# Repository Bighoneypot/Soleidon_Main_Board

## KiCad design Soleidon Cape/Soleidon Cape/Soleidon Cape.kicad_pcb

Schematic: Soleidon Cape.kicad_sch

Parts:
C1, C2, C3, C4, C5, C6, C7, C8: 100nF; C_0201_0603Metric
C9, C10, C11, C12, C13, C14, C15, C16, C17, C18, C19, C20, C21, C22, C23, C24, C25, C26, C27, C28, C29, C30, C31, C32: 22nF; C_0201_0603Metric
C33, C34, C35, C36, C37, C38, C39, C40: C100 nF; C_0201_0603Metric
C41, C55, C56: 10μF; C_0805_2012Metric
C42: C220uF/35V; PCAP_8x10-ELECT_NCA; Part number UWT1V221MNL1GS
C43: 100pF; C_0201_0603Metric
C44: 2.2nF; C_0201_0603Metric
C45: 10uF; C_0201_0603Metric
C46: 10nF; C_0201_0603Metric
C47: 100nf; C_0201_0603Metric
C48: 0.1μF; C_0805_2012Metric
C49: 220uF 50V; CAP_6.3 X 5.8_PAN
C50: 1uF; C_0201_0603Metric
C51: 470nF; C_0201_0603Metric
C52, C58: 22 µF X7R; C_0201_0603Metric
C53: 470pF; C_0805_2012Metric
C54: C220uF/35V; PCAP_8x10-ELECT_NCA; Part number 5YXF220MEFC Rubycon
C57: 220 µF/10 V; PCAP_8x10-ELECT_NCA
D1, D2, D3, D4, D5, D6, D7, D8: D_Zener_4.7V; D_SOD-123
D9, D10: LTST-C190KRKT; LED_0603_1608Metric
D11: MBRS340; D_SMC
D12: Z2SMBxxx; D_SMB
D13: P6SMB33A; DIOM4336X265N; PARTREV F2102
D14: D_Schottky; SMA_DIO_schottky; Part number B240A-13-F
D15: SS54; D_SMA
D16: LED; LED_0603_1608Metric
F1: 01550900DR; FUSE_155900_LTF
H1, H2, H3, H4, H5, H6: MountingHole; MountingHole_3.2mm_M3
J1, J2, J8, J9, J13, J14, J15, J16: Conn_01x01_Socket; PinHeader_1x01_P2.54mm_Vertical
J3: U1_4-20mA; CUI_TBL009-254-04GY-2GY; DigiKey_Part_Number 102-TBL009-254-04GY-2GY-ND
J4: U8_4-20mA; CUI_TBL009-254-04GY-2GY; DigiKey_Part_Number 102-TBL009-254-04GY-2GY-ND
J5: U2_0-5V; CUI_TBL009-254-04GY-2GY; DigiKey_Part_Number 102-TBL009-254-04GY-2GY-ND
J6: U5_0-5V; CUI_TBL009-254-04GY-2GY; DigiKey_Part_Number 102-TBL009-254-04GY-2GY-ND
J7: U6_0-5V; CUI_TBL009-254-04GY-2GY; DigiKey_Part_Number 102-TBL009-254-04GY-2GY-ND
J10: U7_0-5V; CUI_TBL009-254-04GY-2GY; DigiKey_Part_Number 102-TBL009-254-04GY-2GY-ND
J11: U3_0-5V; CUI_TBL009-254-04GY-2GY; DigiKey_Part_Number 102-TBL009-254-04GY-2GY-ND
J12: U4_0-5V; CUI_TBL009-254-04GY-2GY; DigiKey_Part_Number 102-TBL009-254-04GY-2GY-ND
J17: PowerOnOff for Sensors; PinHeader_1x02_P2.54mm_Vertical
J18: 2601-1102; CONN2_2601-1102_WAG
J19, J20, J21, J23, J24, J25, J26, J27, J28: PRT-14417; QWIIC-SPARKFUN_PRT-14417; PARTREV NA
J22: Power OnOff StepDown; PinHeader_1x02_P2.54mm_Vertical
J29, J30: 2-644803-3; TE_2-644803-3; PARTREV R
J31, J32, J33, J35, J36, J37, J39, J40: Power 24V; CONN_1841513
J34: Power 3.3V; CONN_1841513
J38: Power 5V; CONN_1841513
JP1, JP2, JP3, JP4, JP5, JP6, JP7, JP8, JP9, JP10, JP11, JP12, JP13, JP14, JP15, JP16, JP20, JP21, JP22, JP23, JP24, JP25, JP26, JP27, JP28, JP29, JP30, JP35, JP36, JP37, JP38, JP39, JP40, JP41, JP42: SolderJumper_2_Open; SolderJumper-2_P1.3mm_Open_TrianglePad1.0x1.5mm
JP17, JP18, JP19, JP31, JP32, JP33, JP34: SolderJumper_2_Open; Custom_Open_Jumper
JP43: SolderJumper_2_Open; SolderJumper-2_P1.3mm_Open_RoundedPad1.0x1.5mm
L1: 82 μH; RL622_Series; Part number RL622-820K-RC Bourns
L1_SRR1260-330M1: 33 µH; IND_BOURNS_SRR1260
LED1: LED; LED_0603_1608Metric
Q1, Q2, Q3, Q4: BSS138; SOT-23
R1, R2, R3, R4, R5, R6, R7, R8: R10k; R_0603_1608Metric
R9, R10, R43, R44, R45, R46, R47, R48: R0; R_0603_1608Metric
R11, R12, R13, R14, R15, R16, R17, R18, R19, R20, R21, R22, R23, R24, R25, R26, R27, R28, R29, R30, R31, R32, R33, R34: R470Ω; R_0603_1608Metric
R35, R36, R37, R38, R39, R40, R41, R42: 180Ω; R_0603_1608Metric
R49, R50, R51, R52, R53, R59, R61, R68: 10K; R_0603_1608Metric
R54: R100K; C_0201_0603Metric
R55: 4.7kΩ; R_0201_0603Metric
R56: 8.2kΩ; R_1206_3216Metric
R57: R47k; C_0201_0603Metric
R58, R60: 4.7kΩ; R_0603_1608Metric
R62, R64, R65: R0; C_0201_0603Metric
R63: R100Ω; R_0603_1608Metric
R66: R3.8K; C_0201_0603Metric
R67: 100 kΩ; R_0603_1608Metric
R69: 680 Ω; R_0201_0603Metric
R70: 220Ω; R_0201_0603Metric
R71, R72, R73, R74, R75, R76, R77, R78: 4.7kΩ; R_0805_2012Metric
TP1, TP2, TP4, TP7, TP8, TP9, TP11, TP12, TP13, TP14, TP16: TestPoint; TestPoint_Pad_1.5x1.5mm
TP3: 24Vin; TestPoint_Pad_1.5x1.5mm
TP5, TP6: 24Vout; TestPoint_Pad_1.5x1.5mm
TP10: TestPoint_2Pole; PinHeader_1x02_P2.54mm_Vertical
TP15: TestPoint -GND_5V; TestPoint_Pad_1.5x1.5mm
TP17: TestPoint +5V; TestPoint_Pad_1.5x1.5mm
U1, U2, U3, U4, U5, U6, U7, U8: ADS1115IDGSR; DGS0010A_N
U9: TPS5403; SOIC-8_3.9x4.9mm_P1.27mm
U10: PCA9546A TSSOP; D16_TEX
VR1: LM2596S-5.0_NOPB; PARTREV E

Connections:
+3.3V: C45.1, C47.1, C54.1, C55.1, C56.1, J23.2, J24.2, J34.5, J34.6, J34.7, J34.8, JP11.2 (B), JP12.1 (A), JP13.2 (B), JP17.1 (A), JP18.1 (A), JP19.1 (A), JP24.2 (B), JP26.1 (A), JP31.1 (A), JP32.1 (A), JP33.1 (A), JP34.1 (A), L1.2, Q1.1 (G), Q2.1 (G), Q3.1 (G), Q4.1 (G), R58.2, R60.2, R64.1, R68.2, R70.2, R71.1, R72.1, R75.1, R76.1, TP8.1, TP11.1, U10.16 (VCC)
+24V: F1.1, J18.1 (1_1), J18.2 (1_2), TP3.1, TP5.1
+24V_PowerSensor_OUT: J17.1, J31.5, J31.6, J31.7, J31.8, J32.5, J32.6, J32.7, J32.8, J33.5, J33.6, J33.7, J33.8, J35.5, J35.6, J35.7, J35.8, J36.5, J36.6, J36.7, J36.8, J37.5, J37.6, J37.7, J37.8, J39.5, J39.6, J39.7, J39.8, J40.5, J40.6, J40.7, J40.8, R55.1
+24_PROTECT: C41.1, C42.1, C49.1, C50.1, C51.2, D12.1 (K), D13.C, J17.2, J22.2, R56.2, TP2.1, TP6.1, U9.2 (VIN), VR1.1 (VIN)
/2SCL: J23.4, U10.10 (SC2)
/2SDA: J23.3, U10.9 (SD2)
/3SCL: J24.4, U10.12 (SC3)
/3SDA: J24.3, U10.11 (SD3)
/A0: JP12.2 (B), R52.2, U10.1 (A0)
/A1: JP13.1 (A), R51.2, U10.2 (A1)
/A2: JP11.1 (A), R50.2, U10.13 (A2)
ADDR_U8: R46.1, U5.1 (ADDR)
ADDR_U9: R48.1, U6.1 (ADDR)
ADDR_U10: R44.1, U2.1 (ADDR)
ADDR_U11: R45.1, U3.1 (ADDR)
ADDR_U13: R47.1, U4.1 (ADDR)
ADDR_U14: R43.1, U7.1 (ADDR)
ADDR_U16: R10.1, U8.1 (ADDR)
ADDR_U17: R9.1, U1.1 (ADDR)
AIN0_U8: J6.1_A (1), J6.1_B (1), R11.2
AIN0_U9: J7.1_A (1), J7.1_B (1), R16.2
AIN0_U10: J5.1_A (1), J5.1_B (1), R13.2
AIN0_U11: J11.1_A (1), J11.1_B (1), R19.2
AIN0_U13: J12.1_A (1), J12.1_B (1), R23.2
AIN0_U14: J10.1_A (1), J10.1_B (1), R27.2
AIN0_U16: C40.2, D8.2 (A), J4.1_A (1), J4.1_B (1), R42.2, U8.4 (AIN0)
AIN0_U17: C36.2, D4.2 (A), J3.1_A (1), J3.1_B (1), R38.2, U1.4 (AIN0)
AIN1_U8: J6.2_A (2), J6.2_B (2), R31.2
AIN1_U9: J7.2_A (2), J7.2_B (2), R17.2
AIN1_U10: J5.2_A (2), J5.2_B (2), R34.2
AIN1_U11: J11.2_A (2), J11.2_B (2), R20.2
AIN1_U13: J12.2_A (2), J12.2_B (2), R24.2
AIN1_U14: J10.2_A (2), J10.2_B (2), R28.2
AIN1_U16: C39.2, D7.2 (A), J4.2_A (2), J4.2_B (2), R41.2, U8.5 (AIN1)
AIN1_U17: C35.2, D3.2 (A), J3.2_A (2), J3.2_B (2), R37.2, U1.5 (AIN1)
AIN2_U8: J6.3_A (3), J6.3_B (3), R32.2
AIN2_U9: J7.3_A (3), J7.3_B (3), R33.2
AIN2_U10: J5.3_A (3), J5.3_B (3), R14.2
AIN2_U11: J11.3_A (3), J11.3_B (3), R21.2
AIN2_U13: J12.3_A (3), J12.3_B (3), R25.2
AIN2_U14: J10.3_A (3), J10.3_B (3), R29.2
AIN2_U16: C38.2, D6.2 (A), J4.3_A (3), J4.3_B (3), R40.2, U8.6 (AIN2)
AIN2_U17: C34.2, D2.2 (A), J3.3_A (3), J3.3_B (3), R36.2, U1.6 (AIN2)
AIN3_U8: J6.4_A (4), J6.4_B (4), R12.2
AIN3_U9: J7.4_A (4), J7.4_B (4), R18.2
AIN3_U10: J5.4_A (4), J5.4_B (4), R15.2
AIN3_U11: J11.4_A (4), J11.4_B (4), R22.2
AIN3_U13: J12.4_A (4), J12.4_B (4), R26.2
AIN3_U14: J10.4_A (4), J10.4_B (4), R30.2
AIN3_U16: C37.2, D5.2 (A), J4.4_A (4), J4.4_B (4), R39.2, U8.7 (AIN3)
AIN3_U17: C33.2, D1.2 (A), J3.4_A (4), J3.4_B (4), R35.2, U1.7 (AIN3)
ALERT/RDY_U8: J14.1, R5.2, U5.2 (ALERT_RDY)
ALERT/RDY_U10: J9.1, R1.2, U2.2 (ALERT_RDY)
ALERT/RDY_U11: J15.1, R2.2, U3.2 (ALERT_RDY)
ALERT/RDY_U13: J16.1, R3.2, U4.2 (ALERT_RDY)
ALERT/RDY_U14: J13.1, R7.2, U7.2 (ALERT_RDY)
ALERT/RDY_U16: J2.1, R8.2, U8.2 (ALERT_RDY)
ALERT/RDY_U17: J1.1, R4.2, U1.2 (ALERT_RDY)
EXT_5V: C1.1, C2.1, C3.1, C4.1, C5.2, C6.1, C7.1, C8.1, C57.1, C58.1, D15.1 (K), J38.5, J38.6, J38.7, J38.8, JP1.1 (A), JP2.1 (A), JP3.1 (A), JP4.1 (A), JP5.1 (A), JP6.1 (A), JP7.1 (A), JP8.1 (A), JP9.2 (B), JP10.1 (A), JP39.1 (A), JP40.2 (B), JP41.1 (A), JP42.2 (B), L1_SRR1260-330M1.1, L1_SRR1260-330M1.2, R43.2, R48.2, R69.2, R73.1, R74.1, R77.1, R78.2, TP9.1, TP10.2, TP17.1, U1.8 (VDD), U2.8 (VDD), U3.8 (VDD), U4.8 (VDD), U5.8 (VDD), U6.8 (VDD), U7.8 (VDD), U8.8 (VDD), VR1.2 (OUTPUT), VR1.4 (FEEDBACK)
GND: C1.2, C2.2, C3.2, C4.2, C5.1, C6.2, C7.2, C8.2, C9.2, C10.2, C11.2, C12.2, C13.2, C14.2, C15.2, C16.2, C17.2, C18.2, C19.2, C20.2, C21.2, C22.2, C23.2, C24.2, C25.2, C26.2, C27.2, C28.2, C29.2, C30.2, C31.2, C32.2, C33.1, C34.1, C35.1, C36.1, C37.1, C38.1, C39.1, C40.1, C41.2, C42.2, C43.2, C44.2, C45.2, C46.2, C47.2, C49.2, C50.2, C51.1, C54.2, C55.2, C56.2, C57.2, C58.2, D1.1 (K), D2.1 (K), D3.1 (K), D4.1 (K), D5.1 (K), D6.1 (K), D7.1 (K), D8.1 (K), D9.1 (C), D10.1 (C), D12.2 (A), D13.A, D14.2 (A), D15.2 (A), D16.1 (K), J18.3 (2_1), J18.4 (2_2), J19.1, J20.1, J21.1, J23.1, J24.1, J25.1, J26.1, J27.1, J28.1, J29.2, J30.2, J31.1, J31.2, J31.3, J31.4, J32.1, J32.2, J32.3, J32.4, J33.1, J33.2, J33.3, J33.4, J34.1, J34.2, J34.3, J34.4, J35.1, J35.2, J35.3, J35.4, J36.1, J36.2, J36.3, J36.4, J37.1, J37.2, J37.3, J37.4, J38.1, J38.2, J38.3, J38.4, J39.1, J39.2, J39.3, J39.4, J40.1, J40.2, J40.3, J40.4, LED1.1 (K), R35.1, R36.1, R37.1, R38.1, R39.1, R40.1, R41.1, R42.1, R46.2, R47.2, R50.1, R51.1, R52.1, R54.2, R66.2, R67.1, TP1.1, TP4.1, TP10.1, TP12.1, TP15.1, TP16.1, U1.3 (GND), U2.3 (GND), U3.3 (GND), U4.3 (GND), U5.3 (GND), U6.3 (GND), U7.3 (GND), U8.3 (GND), U9.7 (GND), U10.8 (GND), VR1.3 (GROUND), VR1.5 (~ON/OFF), VR1.6 (GND_TAB)
unnamed: C44.1, R57.2
unnamed: C48.2, R62.2
unnamed: C53.1, R64.2, R65.1, TP7.1
unnamed: D9.2 (A), R56.1
unnamed: D10.2 (A), R55.2
unnamed: D11.2 (A), F1.2
unnamed: D11.1 (K), J22.1
unnamed: C48.1, D14.1 (K), L1.1, U9.8 (LX)
unnamed: D16.2 (A), R69.1
unnamed: J29.1, J30.1, TP13.1
unnamed: J29.3, J30.3, TP14.1
unnamed: JP1.2 (B), R1.1
unnamed: JP2.2 (B), R3.1
unnamed: JP3.2 (B), R6.1
unnamed: JP4.2 (B), R2.1
unnamed: JP5.2 (B), R7.1
unnamed: JP6.2 (B), R4.1
unnamed: JP7.2 (B), R5.1
unnamed: JP8.2 (B), R8.1
unnamed: JP9.1 (A), R49.2
unnamed: JP10.2 (B), R53.1
unnamed: J19.3, JP14.2 (B)
unnamed: J20.3, JP15.2 (B)
unnamed: J21.3, JP16.2 (B)
unnamed: J21.2, JP17.2 (B)
unnamed: J19.2, JP18.2 (B)
unnamed: J20.2, JP19.2 (B)
unnamed: J19.4, JP20.2 (B)
unnamed: J20.4, JP21.2 (B)
unnamed: J21.4, JP22.2 (B)
unnamed: JP23.2 (B), R58.1
unnamed: JP24.1 (A), R59.2
unnamed: JP25.2 (B), R60.1
unnamed: JP26.2 (B), R61.1
unnamed: J26.3, JP27.2 (B)
unnamed: J27.3, JP28.2 (B)
unnamed: J25.4, JP29.2 (B)
unnamed: J28.3, JP30.2 (B)
unnamed: J25.2, JP31.2 (B)
unnamed: J26.2, JP32.2 (B)
unnamed: J27.2, JP33.2 (B)
unnamed: J28.2, JP34.2 (B)
unnamed: J26.4, JP35.2 (B)
unnamed: J27.4, JP36.2 (B)
unnamed: J25.3, JP37.2 (B)
unnamed: J28.4, JP38.2 (B)
unnamed: JP39.2 (B), R63.2
unnamed: C52.1, JP40.1 (A)
unnamed: JP41.2 (B), R63.1
unnamed: C52.2, JP42.1 (A)
unnamed: JP43.1 (A), R67.2
unnamed: JP43.2 (B), R68.1, U10.3 (*RESET)
unnamed: LED1.2 (A), R70.1
unnamed: C14.1, R13.1, U2.4 (AIN0)
unnamed: C32.1, R34.1, U2.5 (AIN1)
unnamed: C15.1, R14.1, U2.6 (AIN2)
unnamed: C11.1, R15.1, U2.7 (AIN3)
unnamed: C23.1, R19.1, U3.4 (AIN0)
unnamed: C24.1, R20.1, U3.5 (AIN1)
unnamed: C25.1, R21.1, U3.6 (AIN2)
unnamed: C26.1, R22.1, U3.7 (AIN3)
unnamed: C27.1, R23.1, U4.4 (AIN0)
unnamed: C16.1, R24.1, U4.5 (AIN1)
unnamed: C28.1, R25.1, U4.6 (AIN2)
unnamed: C29.1, R26.1, U4.7 (AIN3)
unnamed: C9.1, R11.1, U5.4 (AIN0)
unnamed: C20.1, R31.1, U5.5 (AIN1)
unnamed: C30.1, R32.1, U5.6 (AIN2)
unnamed: C10.1, R12.1, U5.7 (AIN3)
unnamed: C13.1, R16.1, U6.4 (AIN0)
unnamed: C21.1, R17.1, U6.5 (AIN1)
unnamed: C22.1, C31.1, R18.1, R33.1, U6.6 (AIN2), U6.7 (AIN3)
unnamed: C17.1, R27.1, U7.4 (AIN0)
unnamed: C18.1, R28.1, U7.5 (AIN1)
unnamed: C12.1, R29.1, U7.6 (AIN2)
unnamed: C19.1, R30.1, U7.7 (AIN3)
unnamed: R62.1, U9.1 (BOOT)
unnamed: C43.1, R57.1, U9.6 (COMP)
unnamed: R54.1, U9.3 (ROSC)
unnamed: C46.1, U9.4 (SS)
unnamed: C53.2, R65.2, R66.1, U9.5 (VSENSE)
SCL: R49.1, R59.1
SCL_0: Q3.2 (S), R75.2, U10.4 (SD0)
SCL_1: Q4.2 (S), R76.2, U10.7 (SC1)
SCL_ADS_1: Q4.3 (D), R9.2, R78.1, U1.9 (SDA), U1.10 (SCL), U2.9 (SDA), U2.10 (SCL), U3.9 (SDA), U3.10 (SCL), U4.9 (SDA), U4.10 (SCL), U5.9 (SDA), U5.10 (SCL), U6.9 (SDA), U6.10 (SCL), U7.9 (SDA), U7.10 (SCL), U8.9 (SDA), U8.10 (SCL)
SCL_EXT: JP23.1 (A), JP29.1 (A), U10.14 (SCL)
SCL_EXT2: JP20.1 (A), JP35.1 (A)
SCL_EXT3: JP21.1 (A), JP36.1 (A)
SCL_EXT4: JP22.1 (A), JP38.1 (A)
SCL__ADS_0: Q3.3 (D), R45.2, R77.2
SDA: R53.2, R61.2
SDA_0: Q1.2 (S), R71.2, U10.5 (SC0)
SDA_1: Q2.2 (S), R72.2, U10.6 (SD1)
SDA_ADS_0: Q1.3 (D), R44.2, R73.2
SDA_ADS_1: Q2.3 (D), R10.2, R74.2
SDA_EXT: JP25.1 (A), JP37.1 (A), U10.15 (SDA)
SDA_EXT_2: JP14.1 (A), JP15.1 (A), JP16.1 (A), JP27.1 (A), JP28.1 (A), JP30.1 (A)

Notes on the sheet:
I2C ADDRESS JUMPER
Important!!! zener (<100 pF)
Level Shifter SDA1
*****FIRST ADS1115****
HEADER
Dettaglio layout (importante ora) C19 e C20 → attaccati ai pin 1 (VIN) e 3 (GND) del regolatore. L1 e D12 → compattissimi tra i pin 2 (OUT) e 4 (SW). C21 e C22 → subito dopo L1, con collegamento diretto al piano GND. D10 (TVS) → fisicamente vicino al connettore d'ingresso, prima del fusibile. Piano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
0x4B
ADS TO READ 4-20mA
Sensor 4-20mA
ADC ADS1115
0x4A
MOUNTING HOLES
I²C_MUX
Separazione funzionale “fisica” Nel layer 2, puoi sagomare il piano GND per creare piccole “colle” o “colli” di rame che delimitano le zone: 🔵 Zona Analogica (ADS1115, 4–20 mA) → ritorni filtrati e puliti. 🟠 Zona Digitale (PCA9546A, I²C, LED, MCU) → correnti impulsive. ➡️ Queste due zone non devono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
Ampia area di rame GND attorno al condensatore bulk (es. C49 220 µF). Da questa zona partono: il GND dello step-down 24→5 V, il GND del TPS5403 (5→3.3 V), e il piano GND generale del layer 2.
Level Shifter SDA0
0x48
I2C PULL-UP 5V YES/NO
0x49
I2C PULL-UP 3V YES/NO

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
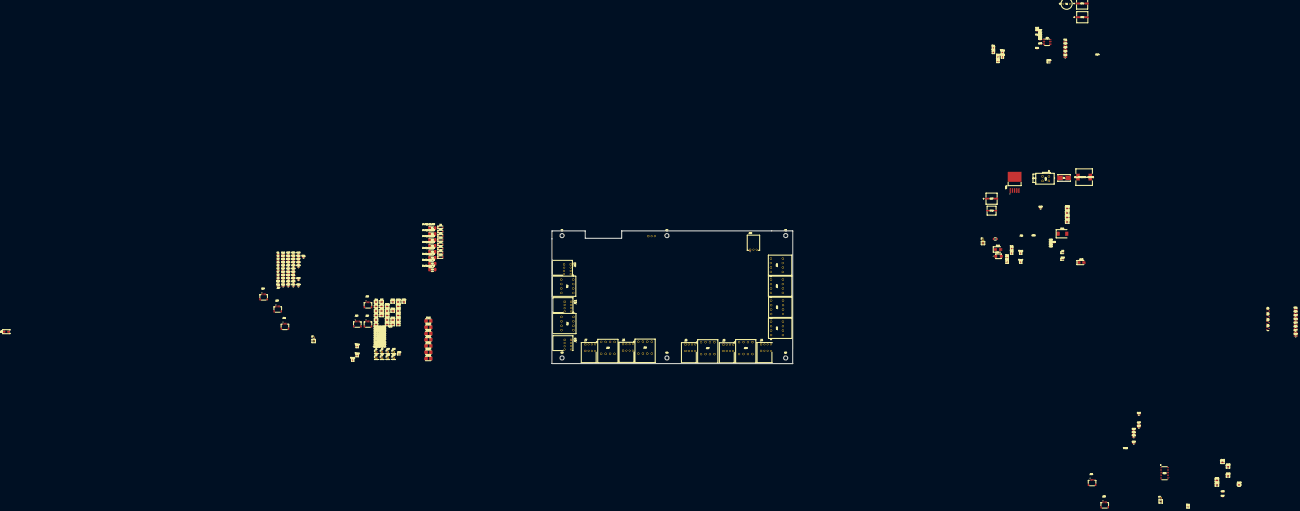
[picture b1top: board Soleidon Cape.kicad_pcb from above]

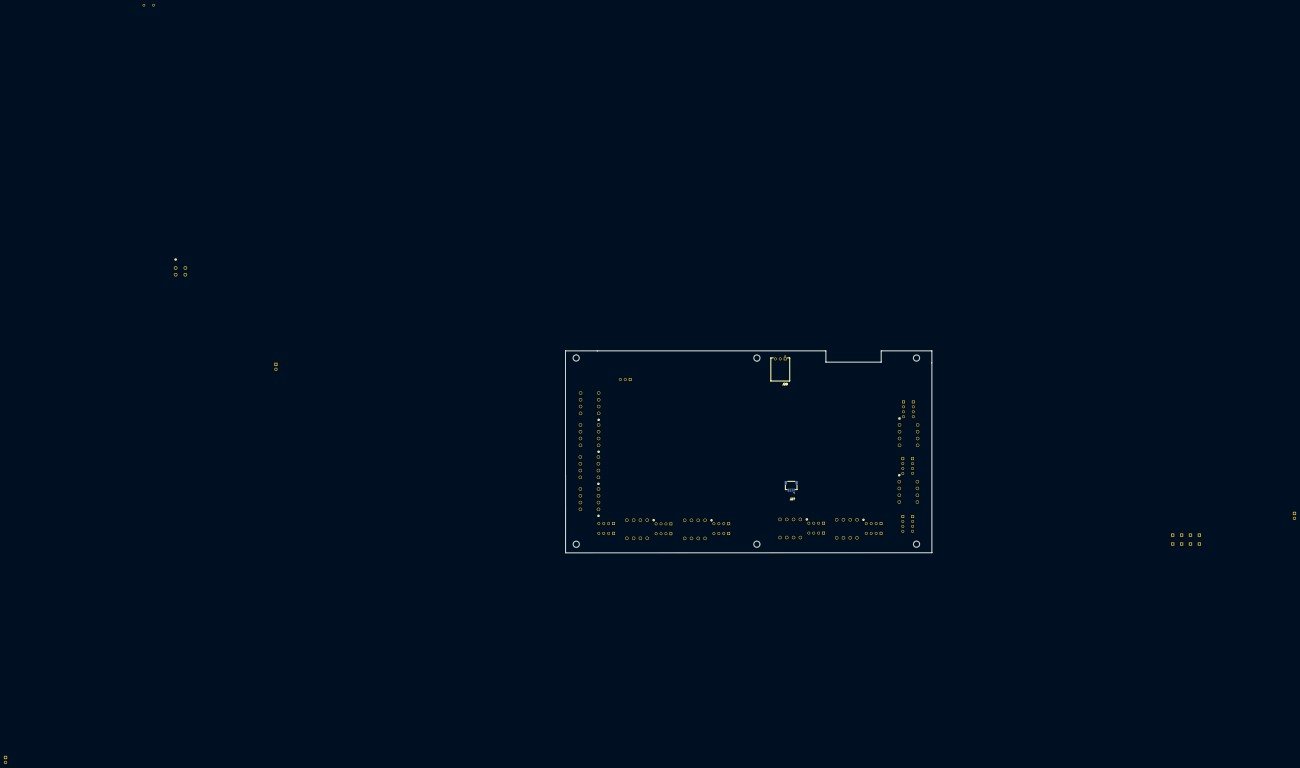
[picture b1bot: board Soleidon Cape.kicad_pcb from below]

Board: 4 copper layers, 277 parts (2 on the bottom side), 158 nets, no tracks yet.

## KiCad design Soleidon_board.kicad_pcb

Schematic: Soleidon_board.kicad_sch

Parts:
C1, C2, C3, C4, C5, C6, C8, C10, C11, C12, C13: 104; C_0805_2012Metric_Pad1.18x1.45mm_HandSolder
C7: 1uF ±10% 50V; CL21A226MAQNNNE; Manufacturer Part CL10A105KB8NNNC; LCSC Part Name 1uF ±10% 50V
C9: 22uF ±20% 25V; CL21A226MAQNNNE; Manufacturer Part CL21A226MAQNNNE; LCSC Part Name 22uF ±20% 25V
C14: 10uF ±10% 16V; CL21A226MAQNNNE; Manufacturer Part CL21A106KOQNNNE; LCSC Part Name 10uF ±10% 16V
CARD1: micro SD-CARD TF PUSH; TF-SMD_TF-PUSH; Manufacturer Part TF PUSH; LCSC Part Name 自弹式 MicroSD卡(TF卡) 卡座
D1, D2, D3: RB168MM-40TR; RB168MM-40TR___SOD-123FL_L2.6-W1.6-LS3.5-RD; Manufacturer Part RB168MM-40TR; LCSC Part Name 电压:40V 电流:1A
H1, H2, H3, H4: MountingHole; MountingHole_3.2mm_M3_ISO14580_Pad_TopOnly
H5: Header-Female-2.54_1x2; PinHeader_1x02_P2.54mm_Vertical; Manufacturer Part 2.54-1*3P母; LCSC Part Name 间距:2.54mm 直插; not fitted
H6: Header-Female-2.54_1x6; PinHeader_1x03_P2.54mm_Vertical; Manufacturer Part 2.54-1*6P母; LCSC Part Name 间距:2.54mm 1x6P 直插; not fitted
H7: Header-Female-2.54_1x3; PinHeader_1x03_P2.54mm_Vertical; Manufacturer Part 2.54-1*3P母; LCSC Part Name 间距:2.54mm 直插; not fitted
H8: Header-Female-2.54_1x2; PinHeader_1x02_P2.54mm_Vertical; Manufacturer Part 2.54-1*2P母; LCSC Part Name 间距:2.54mm 1x2P 直插; not fitted
J1, J2, J3, J4: SM04B-SRSS-TB; CONN_SM04B-SRSS-TB_JST
LED1: TJ-S1615CY6TGLCCSRGB-A5; LED-ARRAY-SMD_4P-L1.6-W1.5-BL-FD; Manufacturer Part TJ-S1615CY6TGLCCSRGB-A5; LCSC Part Name RGB三色
PowerConn1: Header-Female-2.54_1x2; PinSocket_1x03_P2.54mm_Vertical; Manufacturer Part 2.54-1*2P母; LCSC Part Name 间距:2.54mm 1x2P 直插
Q1: PMOSFET-DMP1045U-7; DMP1045_SOT-23-3_L2.9-W1.3-P1.90-LS2.4-BR; Manufacturer Part DMP1045U-7; LCSC Part Name 1个P沟道 耐压:12V 电流:4A
Q2, Q3: 2N3904S-RTK/PS; 2N3904S_SOT-23-3_L2.9-W1.3-P1.90-LS2.4-TR; Manufacturer Part 2N3904S-RTK/PS; LCSC Part Name 2N3904S-RTK/PS
R1, R6, R7, R8, R9: 10K; R_0805_2012Metric_Pad1.20x1.40mm_HandSolder
R2: 22K1; R_0805_2012Metric_Pad1.20x1.40mm_HandSolder
R3: 47K5; R_0805_2012Metric_Pad1.20x1.40mm_HandSolder
R4, R5: 1K; R_0805_2012Metric_Pad1.20x1.40mm_HandSolder
R10, R11, R12, R13, R17, R18: 7.5kΩ; R0603; Manufacturer Part 0603WAF7501T5E; LCSC Part Name 7.5kΩ ±1% 100mW
R14: 150Ω ±1% 62.5mW; R0402; Manufacturer Part RC0402FR-07150RL; LCSC Part Name 150Ω ±1% 62.5mW
R15, R16: 36Ω ±1% 62.5mW; R0402; Manufacturer Part FRC0402J360 TS; LCSC Part Name 36Ω ±1% 62.5mW
S1: 500SSP3S1M6QEA; MFP126DRAUL; Manufacturer_Part_Number 500SSP3S1M6QEA; not fitted
SW1: SW_Push_1P1T-SH_NO_CK_KMR2xxG; Manufacturer Part KMR211NGLFS; LCSC Part Name KMR211NGLFS
TP1, TP2, TP3, TP4, TP5, TP6, TP7, TP8, TP9, TP10, TP11, TP12, TP13, TP14, TP15, TP16, TP17, TP18, TP19, TP20, TP21, TP22, TP23: TestPoint; TestPoint_Pad_D1.0mm
U1: USB4110GFA; GCT_USB4110GFA
U2: CONN-TH_S2B-PH-K-S-GW; Manufacturer Part S2B-PH-K-S-GW; LCSC Part Name 1x2P 间距:2mm 弯插 系列:PH; not fitted
U3: USBLC6-2SC6; SOT-23-6
U4: DFR0819; PinHeader_1x07_P2.54mm_Vertical; not fitted
U5: CP2102N-Axx-xQFN28; QFN-28-1EP_5x5mm_P0.5mm_EP3.35x3.35mm
U6: ESP32-WROVER; Manufacturer Part ESP32-WROVER-E-N4R8; LCSC Part Name 通用型Wi-Fi+BT+BLE MCU模组
Watermeter_WM1: Header-Female-2.54_1x2; JST_GH_SM04B-GHS-TB_1x04-1MP_P1.25mm_Horizontal; Manufacturer Part 2.54-1*2P母; LCSC Part Name 间距:2.54mm 1x2P 直插
boot1: SW_Push_1P1T-SH_NO_CK_KMR2xxG; Manufacturer Part KMR211NGLFS; LCSC Part Name KMR211NGLFS

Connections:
3V3_ON_OFF: C10.2, H6.2, H7.2, TP7.1, TP18.1; also elsewhere on the board
+3V3: C3.1, C4.1, C8.1, C9.2, J2.2 (3V3), J3.2 (3V3), J4.2 (3V3), PowerConn1.3, R4.2, R9.2, TP6.1, TP12.1, TP13.1, U4.1 (VCC), U5.6 (VDD), U5.7 (VREGIN), U6.2 (3V3); also elsewhere on the board
/Battery_Voltage_Monitor_with_MOSFETS/V_Batt_Monitor_INPUT: D1.2 (A), U2.1; also elsewhere on the board
/Buck-Boost3.3V/Buck-Boost_INPUT: D3.1 (C), Q1.2 (S), TP4.1; also elsewhere on the board
/I2C_Connector_Enable/3V3_Input_to_I2C_Connector: C6.2, J1.2 (3V3); also elsewhere on the board
/micro_SD-CARD_enable/3V3_Input_to_micro_SD-CARD: C13.2, CARD1.4 (VDD), R10.2, R11.2, R12.2, R13.2, R17.2, R18.2; also elsewhere on the board
D2: CARD1.7 (DAT0), H7.3, R12.1, U6.24 (IO2)
D4: U6.26 (IO4); also elsewhere on the board
D5: U6.29 (IO5); also elsewhere on the board
D12: H5.1, U6.14 (IO12)
D13: TP9.1, U6.16 (IO13), Watermeter_WM1.3
D14: CARD1.5 (CLX), J2.3 (SDA), R11.1, TP14.1, U6.13 (IO14)
D15: CARD1.3 (CMD), J2.4 (SCL), R10.1, TP15.1, U6.23 (IO15)
D18: U6.30 (IO18); also elsewhere on the board
D19: J3.3 (SDA), TP16.1, U6.31 (IO19)
D21: J1.3 (SDA), J4.3 (SDA), TP20.1, U4.4 (SDA), U6.33 (IO21)
D22: J1.4 (SCL), J4.4 (SCL), TP19.1, U4.3 (SCL), U6.36 (IO22)
D23: J3.4 (SCL), TP17.1, U6.37 (IO23)
D25: U6.10 (IO25); also elsewhere on the board
D26: R15.2, U6.11 (IO26)
D27: R16.2, U6.12 (IO27)
D32: TP11.1, U6.8 (IO32), Watermeter_WM1.4
D33: R14.2, U6.9 (IO33)
D34: C5.1, TP3.1, U6.6 (IO34); also elsewhere on the board
D35: H6.3, TP8.1, U6.7 (IO35)
D+: U3.4 (I/O2), U5.4 (D+)
D-: U3.6 (I/O1), U5.5 (D-)
DN: U1.A7 (DN1), U1.B7 (DN2), U3.1 (I/O1)
DP: U1.A6 (DP1), U1.B6 (DP2), U3.3 (I/O2)
DTR: Q3.1 (E), R7.1, U5.28 (~DTR)
ENA: C7.2, C12.1, C14.2, Q2.3 (C), R9.1, SW1.1, SW1.3, U6.3 (EN)
EXT_5V: D2.1 (C), D3.2 (A), PowerConn1.1, Q1.1 (G), R1.2, TP1.1, TP10.1, Watermeter_WM1.2
GND: C1.2, C2.1, C3.2, C4.2, C5.2, C6.1, C7.1, C8.2, C9.1, C10.1, C11.2, C12.2, C13.1, C14.1, CARD1.6 (VSS), CARD1.10, CARD1.11, CARD1.12, CARD1.13, H6.1, H7.1, J1.1 (GND), J1.5, J1.6, J2.1 (GND), J2.5, J2.6, J3.1 (GND), J3.5, J3.6, J4.1 (GND), J4.5, J4.6, LED1.1 (C), PowerConn1.2, R1.1, R3.2, R6.1, S1.5 (MH_2), SW1.2, SW1.4, TP2.1, TP5.1, U1.A1/B12 (GND), U1.B1/A12 (GND), U1.S1 (GND), U1.S2 (GND), U1.S3 (GND), U1.S4 (GND), U2.2, U3.2 (GND), U4.2 (GND), U5.3 (GND), U5.29 (GND), U6.1 (GND), U6.15 (GND), U6.38 (GND), U6.39 (GND), Watermeter_WM1.1, boot1.2, boot1.4; also elsewhere on the board
IO0: C11.1, H5.2, Q3.3 (C), U6.25 (IO0), boot1.1, boot1.3
unnamed: CARD1.2 (CD/DAT3), R17.1
unnamed: CARD1.8 (DAT1), R13.1
unnamed: CARD1.1 (DAT2), R18.1
unnamed: D1.1 (C), S1.1
unnamed: LED1.2 (B), R16.1, TP21.1
unnamed: LED1.3 (G), R15.1, TP23.1
unnamed: LED1.4 (R), R14.1, TP22.1
unnamed: Q2.2 (B), R7.2
unnamed: Q3.2 (B), R8.2
unnamed: R4.1, R5.2
unnamed: R2.2, R3.1, U5.8 (VBUS)
unnamed: R5.1, U5.9 (~RST)
unnamed: R6.2, U5.11 (~SUSPEND)
RTS: Q2.1 (E), R8.1, U5.24 (~RTS)
RXD0: U5.26 (TXD), U6.34 (RXD0)
SENSOR_VN: H8.1, U6.5 (SENSOR_VN)
SENSOR_VP: H8.2, U6.4 (SENSOR_VP)
TXD0: U5.25 (RXD), U6.35 (TXD0)
VBAT: C2.2, Q1.3 (D), S1.2
VBUS: C1.1, D2.2 (A), R2.1, U1.A4/B9 (VBUS), U1.B4/A9 (VBUS), U3.5 (VBUS)

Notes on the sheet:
3.3V
D14: per SD_MMC_CLK
3V3: per il VDD del mic
GPIO25 will be dedicated to control the NMOSFET that has to connect the line between the battery and the ADC (GPIO34), in order to get the halved battery voltage to be measured.
This screw Terminal has been added for a 5V supply, different from the USB-C (e.g. 5V solar panels,...)
RTC
D33: dedicato al colore RED del led RGB
GND
D2: per SD_MMC_D0 e I2S_SD
MOUNTING HOLES
Decoupling smd ceramic capacitor 0603 package (it should stay as near as possible to 3V3 when designed)
Per comunicare tra ESP32 ed USB
D26: dedicato al colore GREEN del led RGB
Pulsanti di BOOT e RESET.
The three pull-up resistors (smd, 0603 package) should be of values between: 4.7K (faster rise times, supports higher speeds, less prone to signal integrity problems, consumes slightly more power) and 10K (slower, more prone to signal integrity problems, consumes less power)
The ESP32 goes in BOOT when IO0 goes low (IO0 connected directly to GND), and in RESET when ENA goes low (ENA connected directly to GND). The switches have the pins 1 and 2 directly connected, and also the pins 3 and 4. When the button is not being pressed, the pair 1-2 is disconnected from the pai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
D22: per SCL del RTC DFR0819
LED RGB
Condensatori di filtro da mettere all'ingresso dell'alimentazione 3.3V
EXT_5V is coming from the USB-C
D5: per controllare l'NMOS che connette un connettore I2C
D12: per scelta canale L/R del mic
USB to UART converter
Rst
D25: per controllare l'NMOS del Battery V monitor
D27: dedicato al colore BLUE del led RGB
To ensure the power supply to the ESP32 chip during power-up, it is advised to add an RC delay circuit at the EN pin
D15: per SD_MMC_CMD e I2S_WS
SPDT(Single Pole Double Throw) When the battery is connected to the circuit, then if: -the switch is toggled towards 1 --> 2 shorts with 1 (connection to circuit)--> the circuit can be powered by the battery. -the switch is toggled towards 3 --> 2 shorts with 3 (floating) --> the circuit cannot be 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
I2C
USB-C connector
D21: per SDA del RTC DFR0819
These two 1x3 Header Female are used to insert the 6 pin headers of the INMP441 mic.
C_stable_signal_ADC
BOOT
D34: per leggere metà della tensione della batteria
D4: per controllare l'NMOS che connette la micro SD-CARD
Input only pins GPIOs 34 to 39 are GPIs - input only pins. These pins don't have internal pull-up or pull-down resistors. They can't be used as outputs, so use these pins only as inputs: GPIO 34 GPIO 35 GPIO 36 (SENSOR VP) GPIO 39 (SENSOR VN)
Analog to Digital Converter (ADC) The ESP32 has 18 x 12 bits ADC input channels (while the ESP8266 only has 1x 10 bits ADC). These are the GPIOs that can be used as ADC and respective channels: ADC1_CH0 (GPIO 36), ADC1_CH1 (GPIO 37), ADC1_CH2 (GPIO 38), ADC1_CH3 (GPIO 39), ADC1_CH4 (GPIO 32), ADC1_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

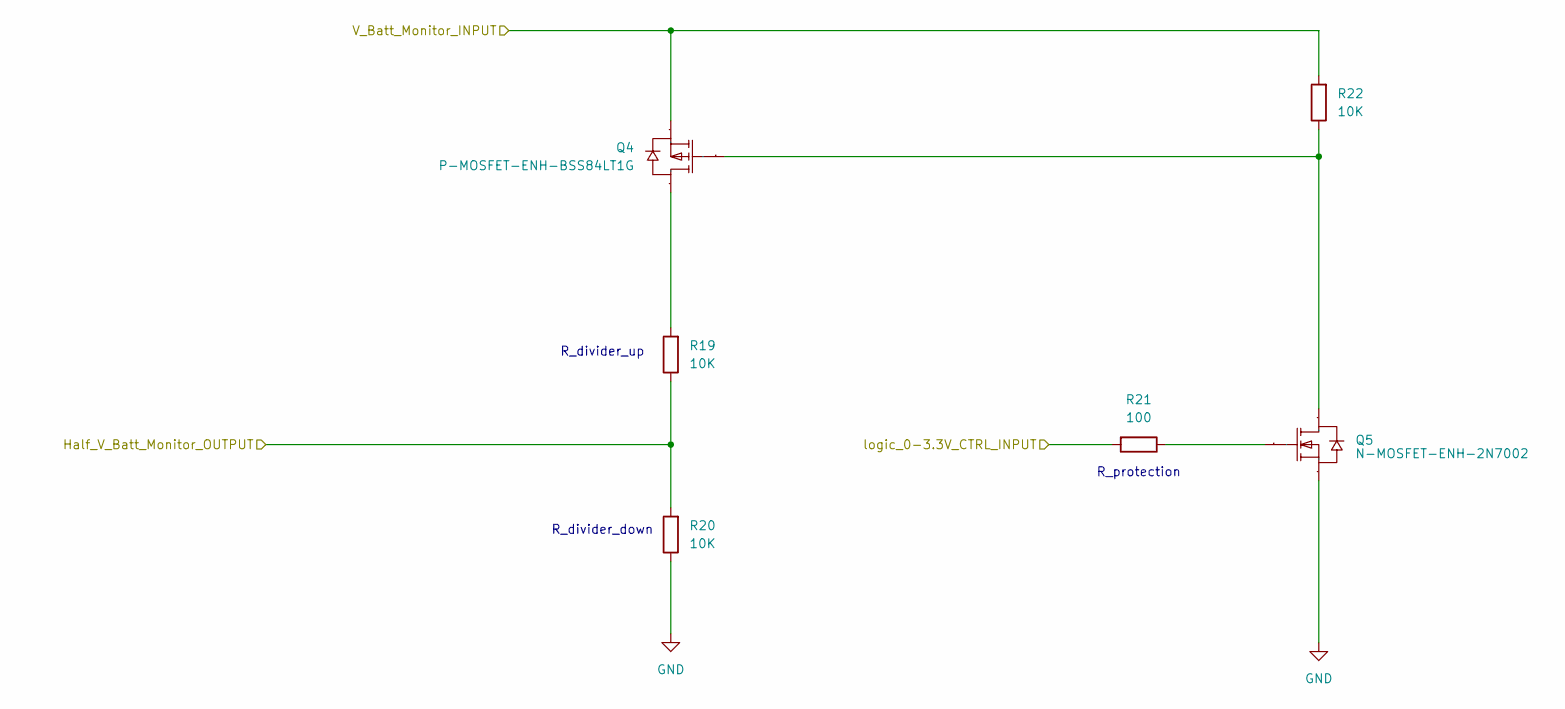
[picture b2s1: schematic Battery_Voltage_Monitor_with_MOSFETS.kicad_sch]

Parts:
Q4: P-MOSFET-ENH-BSS84LT1G; BSS84_SOT-23-3_L2.9-W1.6-P1.90-LS2.8-BR; Manufacturer Part BSS84LT1G; LCSC Part Name 1个P沟道 耐压:50V 电流:130mA
Q5: N-MOSFET-ENH-2N7002; SOT-23-3_L2.9-W1.3-P1.90-LS2.4-BR_2N7002; Manufacturer Part 2N7002; LCSC Part Name 1个N沟道 耐压:60V 电流:115mA
R19, R20, R22: 10K; R_0805_2012Metric_Pad1.20x1.40mm_HandSolder
R21: 100; R_0805_2012Metric_Pad1.20x1.40mm_HandSolder

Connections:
/Battery_Voltage_Monitor_with_MOSFETS/V_Batt_Monitor_INPUT: Q4.2 (S), R22.2; also elsewhere on the board
D25: R21.2; also elsewhere on the board
D34: R19.1, R20.2; also elsewhere on the board
GND: Q5.2 (S), R20.1; also elsewhere on the board
unnamed: Q4.3 (D), R19.2
unnamed: Q4.1 (G), Q5.3 (D), R22.1
unnamed: Q5.1 (G), R21.1

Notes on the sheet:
R_divider_down
R_divider_up
R_protection

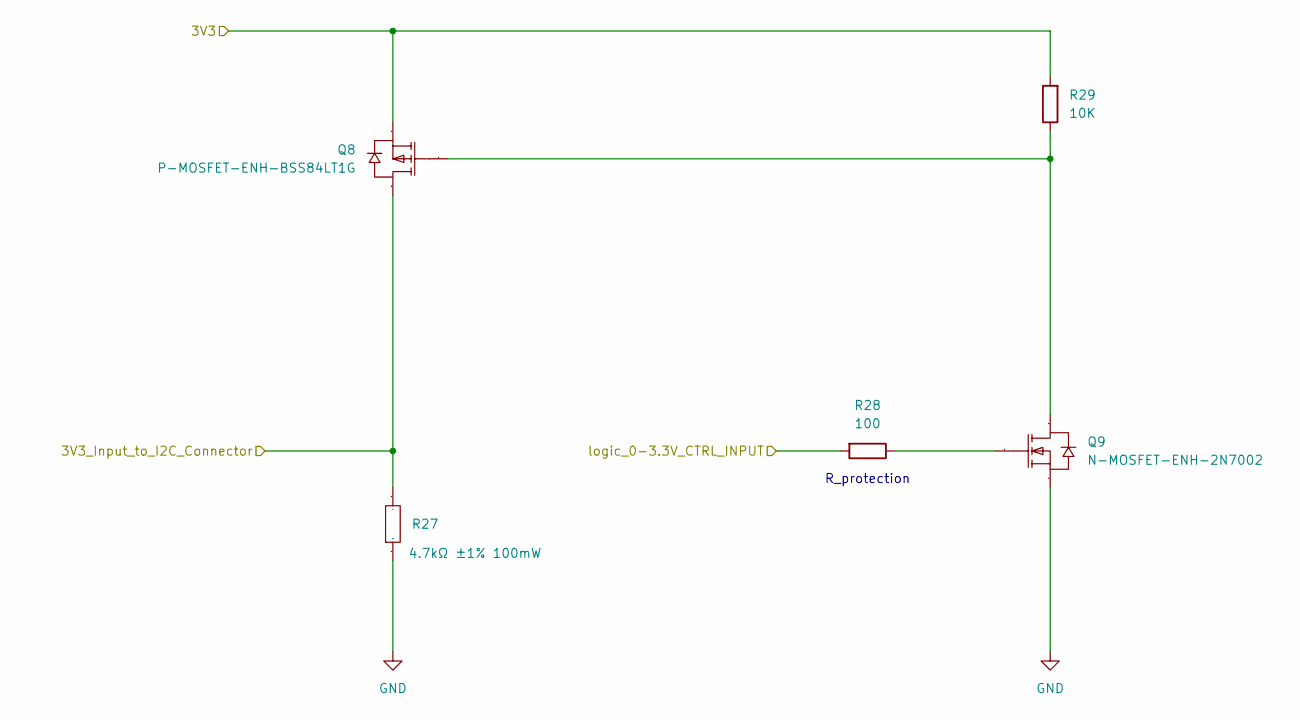
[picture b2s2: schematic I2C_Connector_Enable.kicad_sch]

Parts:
Q8: P-MOSFET-ENH-BSS84LT1G; BSS84_SOT-23-3_L2.9-W1.6-P1.90-LS2.8-BR; Manufacturer Part BSS84LT1G; LCSC Part Name 1个P沟道 耐压:50V 电流:130mA
Q9: N-MOSFET-ENH-2N7002; SOT-23-3_L2.9-W1.3-P1.90-LS2.4-BR_2N7002; Manufacturer Part 2N7002; LCSC Part Name 1个N沟道 耐压:60V 电流:115mA
R27: 4.7kΩ ±1% 100mW; R0603; Manufacturer Part 0603WAF4701T5E; LCSC Part Name 4.7kΩ ±1% 100mW
R28: 100; R_0805_2012Metric_Pad1.20x1.40mm_HandSolder
R29: 10K; R_0805_2012Metric_Pad1.20x1.40mm_HandSolder

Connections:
+3V3: Q8.2 (S), R29.2; also elsewhere on the board
/I2C_Connector_Enable/3V3_Input_to_I2C_Connector: Q8.3 (D), R27.2; also elsewhere on the board
D5: R28.2; also elsewhere on the board
GND: Q9.2 (S), R27.1; also elsewhere on the board
unnamed: Q8.1 (G), Q9.3 (D), R29.1
unnamed: Q9.1 (G), R28.1

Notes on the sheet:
R_protection

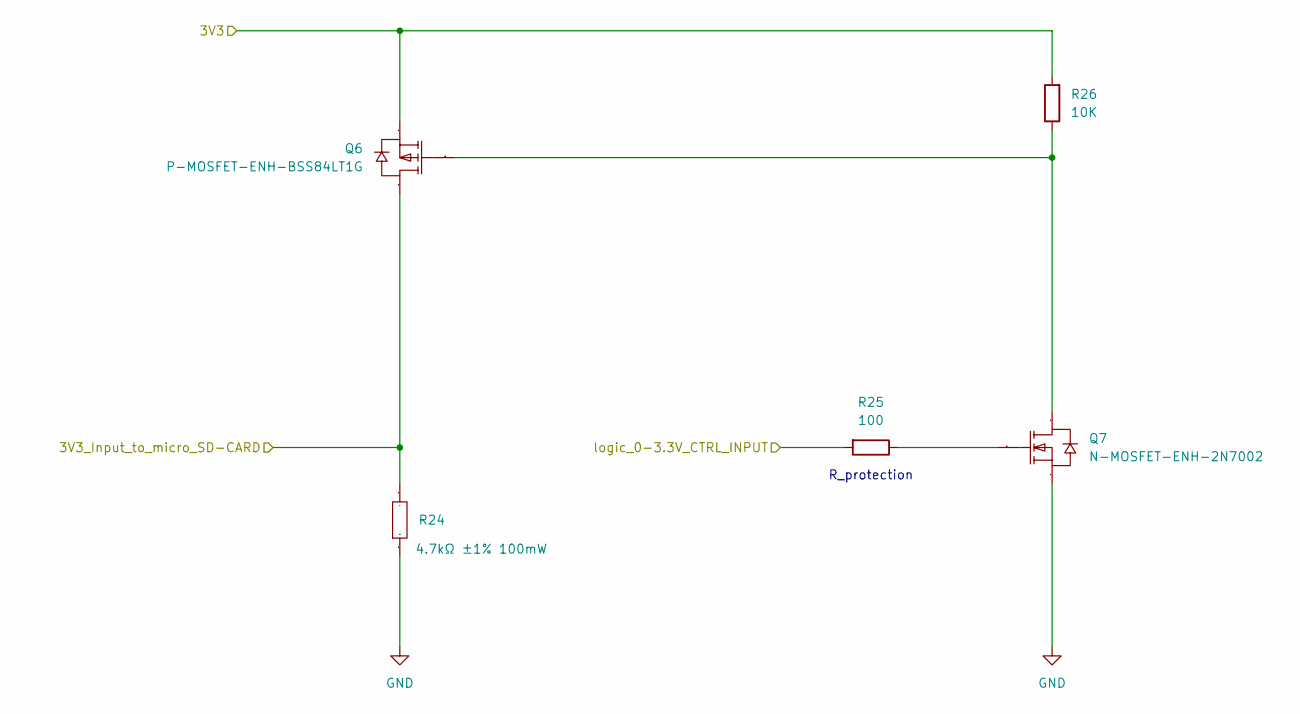
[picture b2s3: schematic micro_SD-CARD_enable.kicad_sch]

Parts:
Q6: P-MOSFET-ENH-BSS84LT1G; BSS84_SOT-23-3_L2.9-W1.6-P1.90-LS2.8-BR; Manufacturer Part BSS84LT1G; LCSC Part Name 1个P沟道 耐压:50V 电流:130mA
Q7: N-MOSFET-ENH-2N7002; SOT-23-3_L2.9-W1.3-P1.90-LS2.4-BR_2N7002; Manufacturer Part 2N7002; LCSC Part Name 1个N沟道 耐压:60V 电流:115mA
R24: 4.7kΩ ±1% 100mW; R0603; Manufacturer Part 0603WAF4701T5E; LCSC Part Name 4.7kΩ ±1% 100mW
R25: 100; R_0805_2012Metric_Pad1.20x1.40mm_HandSolder
R26: 10K; R_0805_2012Metric_Pad1.20x1.40mm_HandSolder

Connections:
+3V3: Q6.2 (S), R26.2; also elsewhere on the board
/micro_SD-CARD_enable/3V3_Input_to_micro_SD-CARD: Q6.3 (D), R24.2; also elsewhere on the board
D4: R25.2; also elsewhere on the board
GND: Q7.2 (S), R24.1; also elsewhere on the board
unnamed: Q6.1 (G), Q7.3 (D), R26.1
unnamed: Q7.1 (G), R25.1

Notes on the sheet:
R_protection

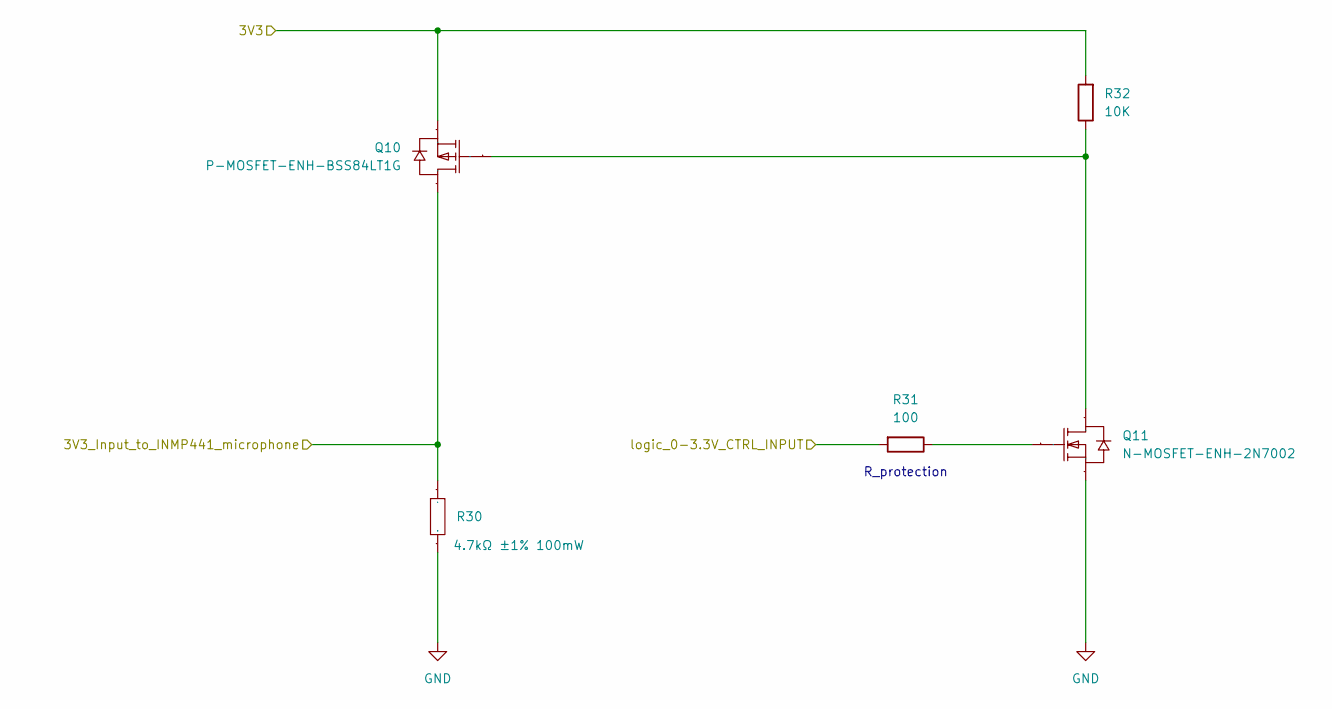
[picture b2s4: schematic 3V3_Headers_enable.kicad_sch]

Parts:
Q10: P-MOSFET-ENH-BSS84LT1G; BSS84_SOT-23-3_L2.9-W1.6-P1.90-LS2.8-BR; Manufacturer Part BSS84LT1G; LCSC Part Name 1个P沟道 耐压:50V 电流:130mA
Q11: N-MOSFET-ENH-2N7002; SOT-23-3_L2.9-W1.3-P1.90-LS2.4-BR_2N7002; Manufacturer Part 2N7002; LCSC Part Name 1个N沟道 耐压:60V 电流:115mA
R30: 4.7kΩ ±1% 100mW; R0603; Manufacturer Part 0603WAF4701T5E; LCSC Part Name 4.7kΩ ±1% 100mW
R31: 100; R_0805_2012Metric_Pad1.20x1.40mm_HandSolder
R32: 10K; R_0805_2012Metric_Pad1.20x1.40mm_HandSolder

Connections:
3V3_ON_OFF: Q10.3 (D), R30.2; also elsewhere on the board
+3V3: Q10.2 (S), R32.2; also elsewhere on the board
D18: R31.2; also elsewhere on the board
GND: Q11.2 (S), R30.1; also elsewhere on the board
unnamed: Q10.1 (G), Q11.3 (D), R32.1
unnamed: Q11.1 (G), R31.1

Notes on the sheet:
R_protection

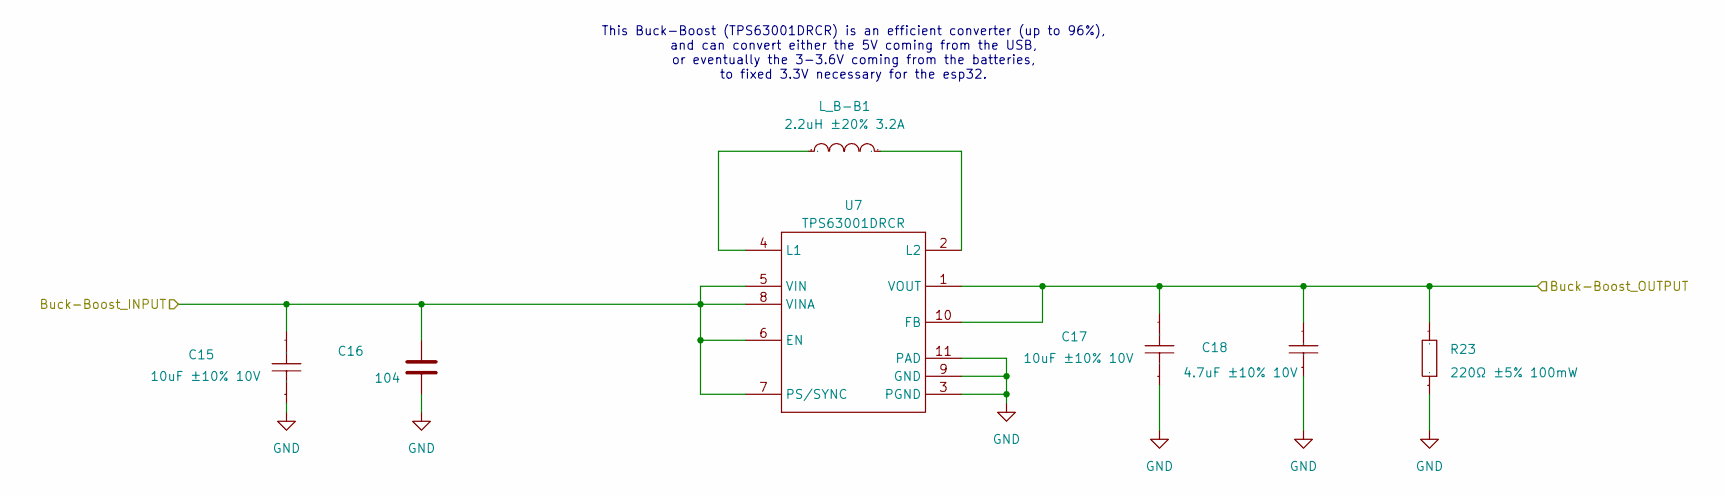
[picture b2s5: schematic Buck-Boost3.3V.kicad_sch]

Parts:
C15, C17: 10uF ±10% 10V; CL21A226MAQNNNE; Manufacturer Part CL10A106KP8NNNC; LCSC Part Name 10uF ±10% 10V
C16: 104; C_0805_2012Metric_Pad1.18x1.45mm_HandSolder
C18: 4.7uF; CL21A226MAQNNNE; Manufacturer Part CL10A475KP8NNNC; LCSC Part Name 4.7uF ±10% 10V
L_B-B1: 2.2uH ±20% 3.2A; SWPA_2_2_IND-SMD_L4.0-W4.0_SWPA4018S; Manufacturer Part SWPA4018S2R2MT; LCSC Part Name 2.2uH ±20% 3.2A
R23: 220Ω; R0603; Manufacturer Part 0603WAJ0221T5E; LCSC Part Name 220Ω ±5% 100mW
U7: TPS63001DRCR; TPS74901DRCR_tps6300; Manufacturer Part TPS63001DRCR; LCSC Part Name 高效率单电感升降压转换器

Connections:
+3V3: C17.2, C18.2, R23.2, U7.1 (VOUT), U7.10 (FB); also elsewhere on the board
/Buck-Boost3.3V/Buck-Boost_INPUT: C15.2, C16.1, U7.5 (VIN), U7.6 (EN), U7.7 (PS/SYNC), U7.8 (VINA); also elsewhere on the board
GND: C15.1, C16.2, C17.1, C18.1, R23.1, U7.3 (PGND), U7.9 (GND), U7.11 (PAD); also elsewhere on the board
unnamed: L_B-B1.1, U7.4 (L1)
unnamed: L_B-B1.2, U7.2 (L2)

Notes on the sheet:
This Buck-Boost (TPS63001DRCR) is an efficient converter (up to 96%), and can convert either the 5V coming from the USB, or eventually the 3-3.6V coming from the batteries, to fixed 3.3V necessary for the esp32.
